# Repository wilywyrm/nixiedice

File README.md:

# nixiedice
Glorified RNG using a Nixie display and pretty LEDs

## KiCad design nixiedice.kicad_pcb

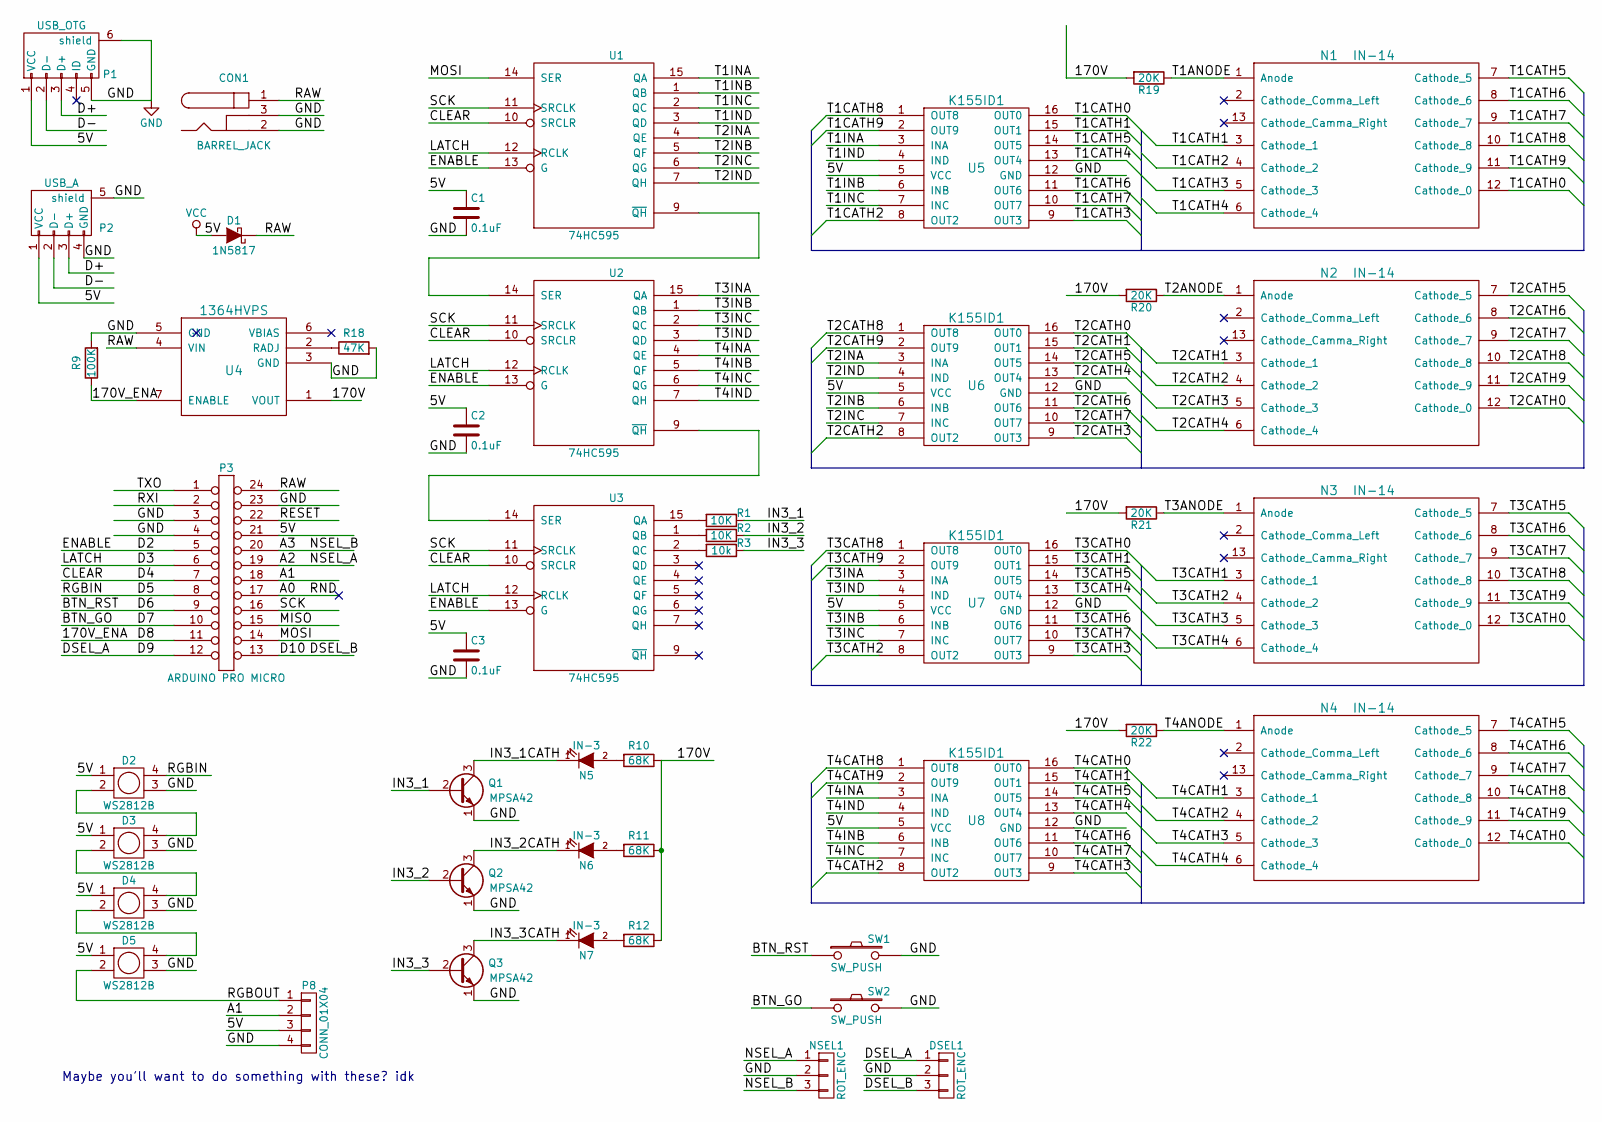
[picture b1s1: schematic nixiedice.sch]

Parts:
C1, C2, C3: 0.1uF; C_Disc_D3_P2.5
CON1: BARREL_JACK
D1: 1N5817; DO-41
D2, D3, D4, D5: WS2812B; LED_WS2812B-PLCC4
DSEL1: ROT_ENC; Socket_Strip_Straight_1x03
N1, N2, N3, N4: IN-14
N5, N6, N7: IN-3
NSEL1: ROT_ENC; Socket_Strip_Straight_1x03
P1: USB_OTG; USB_Micro-B
P2: USB_A
P3: ARDUINO PRO MICRO; Pro_Micro
P8: CONN_01X04; Socket_Strip_Straight_1x04
Q1, Q2, Q3: MPSA42; TO-92_Inline_Wide
R1, R2: 10K; R3
R3: 10k; R3
R9: 100K; R3
R10, R11, R12: 68K; R3
R18: 47K; R3
R19, R20, R21, R22: 20K; R3
SW1, SW2: SW_PUSH; CHERRY_PCB_100H
U1, U2, U3: 74HC595; SOIC-16_3.9x9.9mm_Pitch1.27mm
U4: 1364HVPS
U5, U6, U7, U8: K155ID1; DIP-16_W7.62mm_LongPads

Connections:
/170V: R10.1, R11.1, R12.1, R19.2, R20.2, R21.2, R22.2, U4.1 (VOUT)
/170V_ENA: P3.11, R9.1, U4.7 (ENABLE)
/A0: P3.17
/A1: P3.18, P8.2
/A2: NSEL1.1, P3.19
/A3: NSEL1.3, P3.20
/BTN_GO: P3.10, SW2.1
/BTN_RST: P3.9, SW1.1
/CLEAR: P3.7, U1.10 (SRCLR), U2.10 (SRCLR), U3.10 (SRCLR)
/D2: P3.5, U1.13 (G), U2.13 (G), U3.13 (G)
/D3: P3.6, U1.12 (RCLK), U2.12 (RCLK), U3.12 (RCLK)
/D5: D2.4 (P2), P3.8
/D9: DSEL1.1, P3.12
/D10: DSEL1.3, P3.13
/D+: P1.3 (D+), P2.3 (D+)
/D-: P1.2 (D-), P2.2 (D-)
/IN3_1: Q1.2 (B), R1.1
/IN3_1CATH: N5.1 (K), Q1.3 (C)
/IN3_2: Q2.2 (B), R2.1
/IN3_2CATH: N6.1 (K), Q2.3 (C)
/IN3_3: Q3.2 (B), R3.1
/IN3_3CATH: N7.1 (K), Q3.3 (C)
/MISO: P3.15
/MOSI: P3.14, U1.14 (SER)
/RAW: CON1.1, D1.1 (K), P3.24, U4.4 (VIN)
/RESET: P3.22
/RGBOUT: D5.2 (P3), P8.1
/RXI: P3.2
/SCK: P3.16, U1.11 (SRCLK), U2.11 (SRCLK), U3.11 (SRCLK)
/T1ANODE: N1.1 (Anode), R19.1
/T1CATH0: N1.12 (Cathode_0), U5.16 (OUT0)
/T1CATH1: N1.3 (Cathode_1), U5.15 (OUT1)
/T1CATH2: N1.4 (Cathode_2), U5.8 (OUT2)
/T1CATH3: N1.5 (Cathode_3), U5.9 (OUT3)
/T1CATH4: N1.6 (Cathode_4), U5.13 (OUT4)
/T1CATH5: N1.7 (Cathode_5), U5.14 (OUT5)
/T1CATH6: N1.8 (Cathode_6), U5.11 (OUT6)
/T1CATH7: N1.9 (Cathode_7), U5.10 (OUT7)
/T1CATH8: N1.10 (Cathode_8), U5.1 (OUT8)
/T1CATH9: N1.11 (Cathode_9), U5.2 (OUT9)
/T1INA: U1.15 (QA), U5.3 (INA)
/T1INB: U1.1 (QB), U5.6 (INB)
/T1INC: U1.2 (QC), U5.7 (INC)
/T1IND: U1.3 (QD), U5.4 (IND)
/T2ANODE: N2.1 (Anode), R20.1
/T2CATH0: N2.12 (Cathode_0), U6.16 (OUT0)
/T2CATH1: N2.3 (Cathode_1), U6.15 (OUT1)
/T2CATH2: N2.4 (Cathode_2), U6.8 (OUT2)
/T2CATH3: N2.5 (Cathode_3), U6.9 (OUT3)
/T2CATH4: N2.6 (Cathode_4), U6.13 (OUT4)
/T2CATH5: N2.7 (Cathode_5), U6.14 (OUT5)
/T2CATH6: N2.8 (Cathode_6), U6.11 (OUT6)
/T2CATH7: N2.9 (Cathode_7), U6.10 (OUT7)
/T2CATH8: N2.10 (Cathode_8), U6.1 (OUT8)
/T2CATH9: N2.11 (Cathode_9), U6.2 (OUT9)
/T2INA: U1.4 (QE), U6.3 (INA)
/T2INB: U1.5 (QF), U6.6 (INB)
/T2INC: U1.6 (QG), U6.7 (INC)
/T2IND: U1.7 (QH), U6.4 (IND)
/T3ANODE: N3.1 (Anode), R21.1
/T3CATH0: N3.12 (Cathode_0), U7.16 (OUT0)
/T3CATH1: N3.3 (Cathode_1), U7.15 (OUT1)
/T3CATH2: N3.4 (Cathode_2), U7.8 (OUT2)
/T3CATH3: N3.5 (Cathode_3), U7.9 (OUT3)
/T3CATH4: N3.6 (Cathode_4), U7.13 (OUT4)
/T3CATH5: N3.7 (Cathode_5), U7.14 (OUT5)
/T3CATH6: N3.8 (Cathode_6), U7.11 (OUT6)
/T3CATH7: N3.9 (Cathode_7), U7.10 (OUT7)
/T3CATH8: N3.10 (Cathode_8), U7.1 (OUT8)
/T3CATH9: N3.11 (Cathode_9), U7.2 (OUT9)
/T3INA: U2.15 (QA), U7.3 (INA)
/T3INB: U2.1 (QB), U7.6 (INB)
/T3INC: U2.2 (QC), U7.7 (INC)
/T3IND: U2.3 (QD), U7.4 (IND)
/T4ANODE: N4.1 (Anode), R22.1
/T4CATH0: N4.12 (Cathode_0), U8.16 (OUT0)
/T4CATH1: N4.3 (Cathode_1), U8.15 (OUT1)
/T4CATH2: N4.4 (Cathode_2), U8.8 (OUT2)
/T4CATH3: N4.5 (Cathode_3), U8.9 (OUT3)
/T4CATH4: N4.6 (Cathode_4), U8.13 (OUT4)
/T4CATH5: N4.7 (Cathode_5), U8.14 (OUT5)
/T4CATH6: N4.8 (Cathode_6), U8.11 (OUT6)
/T4CATH7: N4.9 (Cathode_7), U8.10 (OUT7)
/T4CATH8: N4.10 (Cathode_8), U8.1 (OUT8)
/T4CATH9: N4.11 (Cathode_9), U8.2 (OUT9)
/T4INA: U2.4 (QE), U8.3 (INA)
/T4INB: U2.5 (QF), U8.6 (INB)
/T4INC: U2.6 (QG), U8.7 (INC)
/T4IND: U2.7 (QH), U8.4 (IND)
/TXO: P3.1
GND: C1.2, C2.2, C3.2, CON1.2, CON1.3, D2.3 (P4), D3.3 (P4), D4.3 (P4), D5.3 (P4), DSEL1.2, NSEL1.2, P1.5 (GND), P1.6 (shield), P2.4 (GND), P2.5 (shield), P3.3, P3.4, P3.23, P8.4, Q1.1 (E), Q2.1 (E), Q3.1 (E), R9.2, R18.2, SW1.2, SW2.2, U1.8 (GND), U2.8 (GND), U3.8 (GND), U4.3 (GND), U4.5 (GND), U5.12 (GND), U6.12 (GND), U7.12 (GND), U8.12 (GND)
unnamed: D2.2 (P3), D3.4 (P2)
unnamed: D3.2 (P3), D4.4 (P2)
unnamed: D4.2 (P3), D5.4 (P2)
unnamed: N5.2 (A), R10.2
unnamed: N6.2 (A), R11.2
unnamed: N7.2 (A), R12.2
unnamed: R1.2, U3.15 (QA)
unnamed: R2.2, U3.1 (QB)
unnamed: R3.2, U3.2 (QC)
unnamed: R18.1, U4.2 (RADJ)
unnamed: U1.9 (~QH), U2.14 (SER)
unnamed: U2.9 (~QH), U3.14 (SER)
VCC: C1.1, C2.1, C3.1, D1.2 (A), D2.1, D3.1, D4.1, D5.1, P1.1 (VCC), P2.1 (VCC), P3.21, P8.3, U1.16 (VCC), U2.16 (VCC), U3.16 (VCC), U5.5 (VCC), U6.5 (VCC), U7.5 (VCC), U8.5 (VCC)

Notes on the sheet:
Maybe you'll want to do something with these? idk

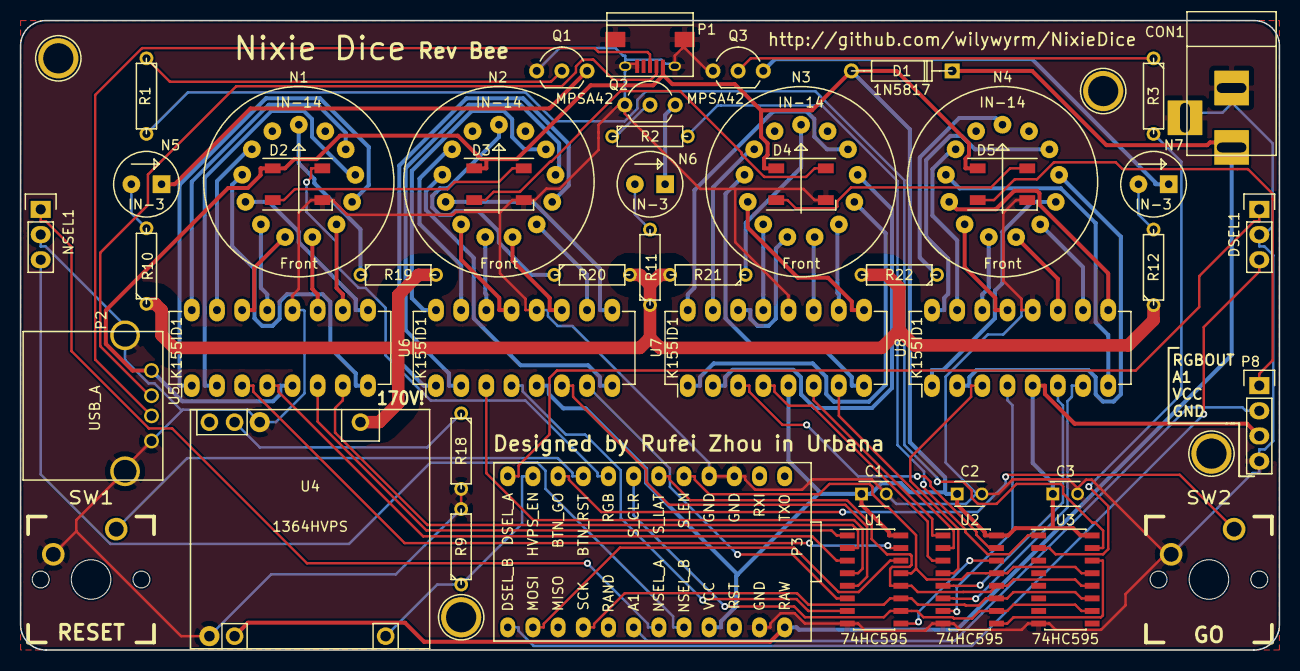
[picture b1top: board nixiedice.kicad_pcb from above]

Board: 2 copper layers, 127.0 x 63.5 mm, 51 parts (0 on the bottom side), 99 nets.

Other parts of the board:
M1, M2, M3, M4: 1pin

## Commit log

2017-01-02 :tada: Added .gitattributes
2017-01-03 fix sleep color
    it is no longer (b,0,0) all over me
2017-01-05 fix IN-14 footprint being upside down
    ussr datasheet is backwards af
2017-01-05 fix indicator IN3 not working
    forgot how to bitwise clear
    also roughly synchronize LED theatre chase with IN3 indicator theatre
    chase effect during dice roll
2017-01-05 change microusb connector to use smd pads
    also add line on front silkscreen to plug this schweet repo
2017-01-06 update silkscreen
2017-01-06 switch mapping for rev A boards to work backwards
2017-01-14 bunch of fixes, tested with rev A board in hand
    - fix setDigit to use MSB order of K155ID1 driver chip while using LSB
    for everything else
    - fix setDigit not negating half of shift register byte
    - fix setAllDigits not separating digits of input properly
    - fix setIndicator not selecting correct indicator IN3
    - fix off by one errors in various indicator effects
2017-01-14 fix maintenance mode crash
    - remove maintenance mode saving of indicator IN3 state, was forcing
    reset in middle of maintenance mode
2017-01-14 switch pins and effect offsets back for rev B
2017-01-14 fix IN3 offsets
2017-01-14 fix indicator display while rolling
2017-02-08 emergency pcb silkscreen revision
2017-02-08 restore last nsel/dsel on exit from maintenance mode
